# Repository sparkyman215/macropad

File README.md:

# macropad
### a small project to practice designing pcbs for keyboards.
Nothing fancy, just a 4x4 macropad with qmk functionality.

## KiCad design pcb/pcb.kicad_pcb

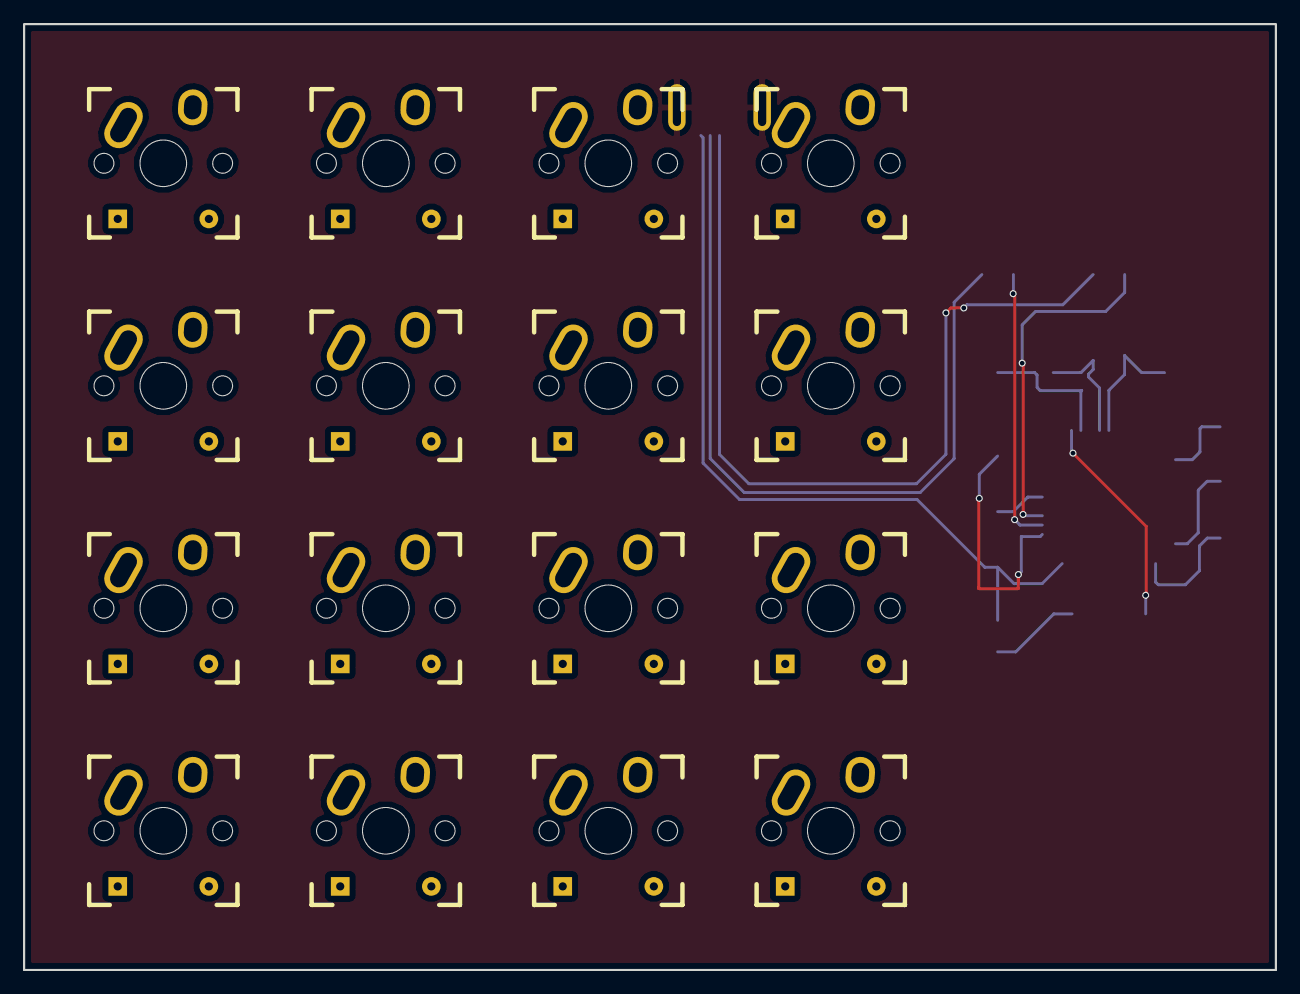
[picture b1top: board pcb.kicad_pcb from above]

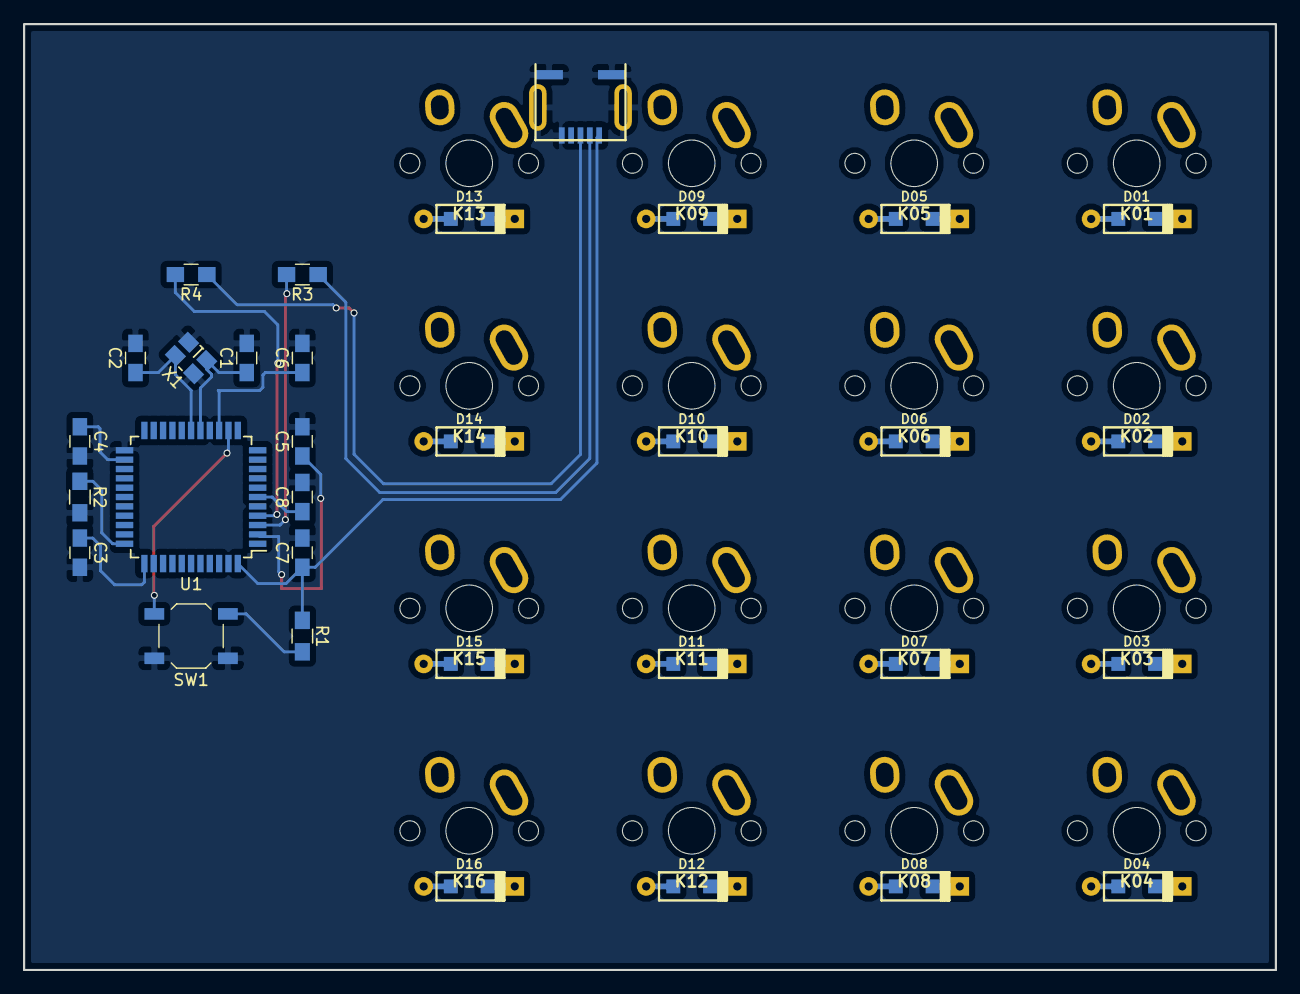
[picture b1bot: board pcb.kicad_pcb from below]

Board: 2 copper layers, 107.2 x 81.0 mm, 48 parts (32 on the bottom side), 35 nets.

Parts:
C1, C2: 22p; C_0805_HandSoldering
C3, C4, C5, C6: 0.1u; C_0805_HandSoldering
C7: 4.7u; C_0805_HandSoldering
C8: 1u; C_0805_HandSoldering
D01, D02, D03, D04, D05, D06, D07, D08, D09, D10, D11, D12, D13, D14, D15, D16: D; D_SOD123_axial
J1: USB_mini_micro_B; USB_miniB_hirose_5S8
K01, K02, K03, K04, K05, K06, K07, K08, K09, K10, K11, K12, K13, K14, K15, K16: KEYSW; Mx_Alps_100
R1, R2: 10k; R_0805_HandSoldering
R3, R4: 22; R_0805_HandSoldering
SW1: SW_PUSH; SW_SPST_TL3342
U1: ATMEGA32U4; TQFP-44_10x10mm_Pitch0.8mm
X1: XTAL_GND; crystal_FA238-TSX3225

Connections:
/col0: K01.1, K02.1, K03.1, K04.1, U1.37
/col1: K05.1, K06.1, K07.1, K08.1, U1.36
/col2: K09.1, K10.1, K11.1, K12.1, U1.32
/col3: K13.1, K14.1, K15.1, K16.1, U1.31
/row0: D01.1, D05.1, D09.1, D13.1, U1.41
/row1: D02.1, D06.1, D10.1, D14.1, U1.40
/row2: D03.1, D07.1, D11.1, D15.1, U1.39
/row3: D04.1, D08.1, D12.1, D16.1, U1.38
GND: C1.2, C2.2, C3.2, C4.2, C5.2, C6.2, C7.2, C8.2, J1.5, J1.6, R2.2, SW1.1, U1.5, U1.15, U1.23, U1.35, U1.43, X1.3
unnamed: C1.1, U1.16, X1.1
unnamed: C2.1, U1.17, X1.2
unnamed: C8.1, U1.6
unnamed: D01.2, K01.2
unnamed: D02.2, K02.2
unnamed: D03.2, K03.2
unnamed: D04.2, K04.2
unnamed: D05.2, K05.2
unnamed: D06.2, K06.2
unnamed: D07.2, K07.2
unnamed: D08.2, K08.2
unnamed: D09.2, K09.2
unnamed: D10.2, K10.2
unnamed: D11.2, K11.2
unnamed: D12.2, K12.2
unnamed: D13.2, K13.2
unnamed: D14.2, K14.2
unnamed: D15.2, K15.2
unnamed: D16.2, K16.2
unnamed: J1.2, R3.1
unnamed: J1.3, R4.1
unnamed: R1.2, SW1.2, U1.13
unnamed: R2.1, U1.33
unnamed: R3.2, U1.3
unnamed: R4.2, U1.4
VCC: C3.1, C4.1, C5.1, C6.1, C7.1, J1.1, R1.1, U1.2, U1.14, U1.24, U1.34, U1.44

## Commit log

2017-09-24 progress
